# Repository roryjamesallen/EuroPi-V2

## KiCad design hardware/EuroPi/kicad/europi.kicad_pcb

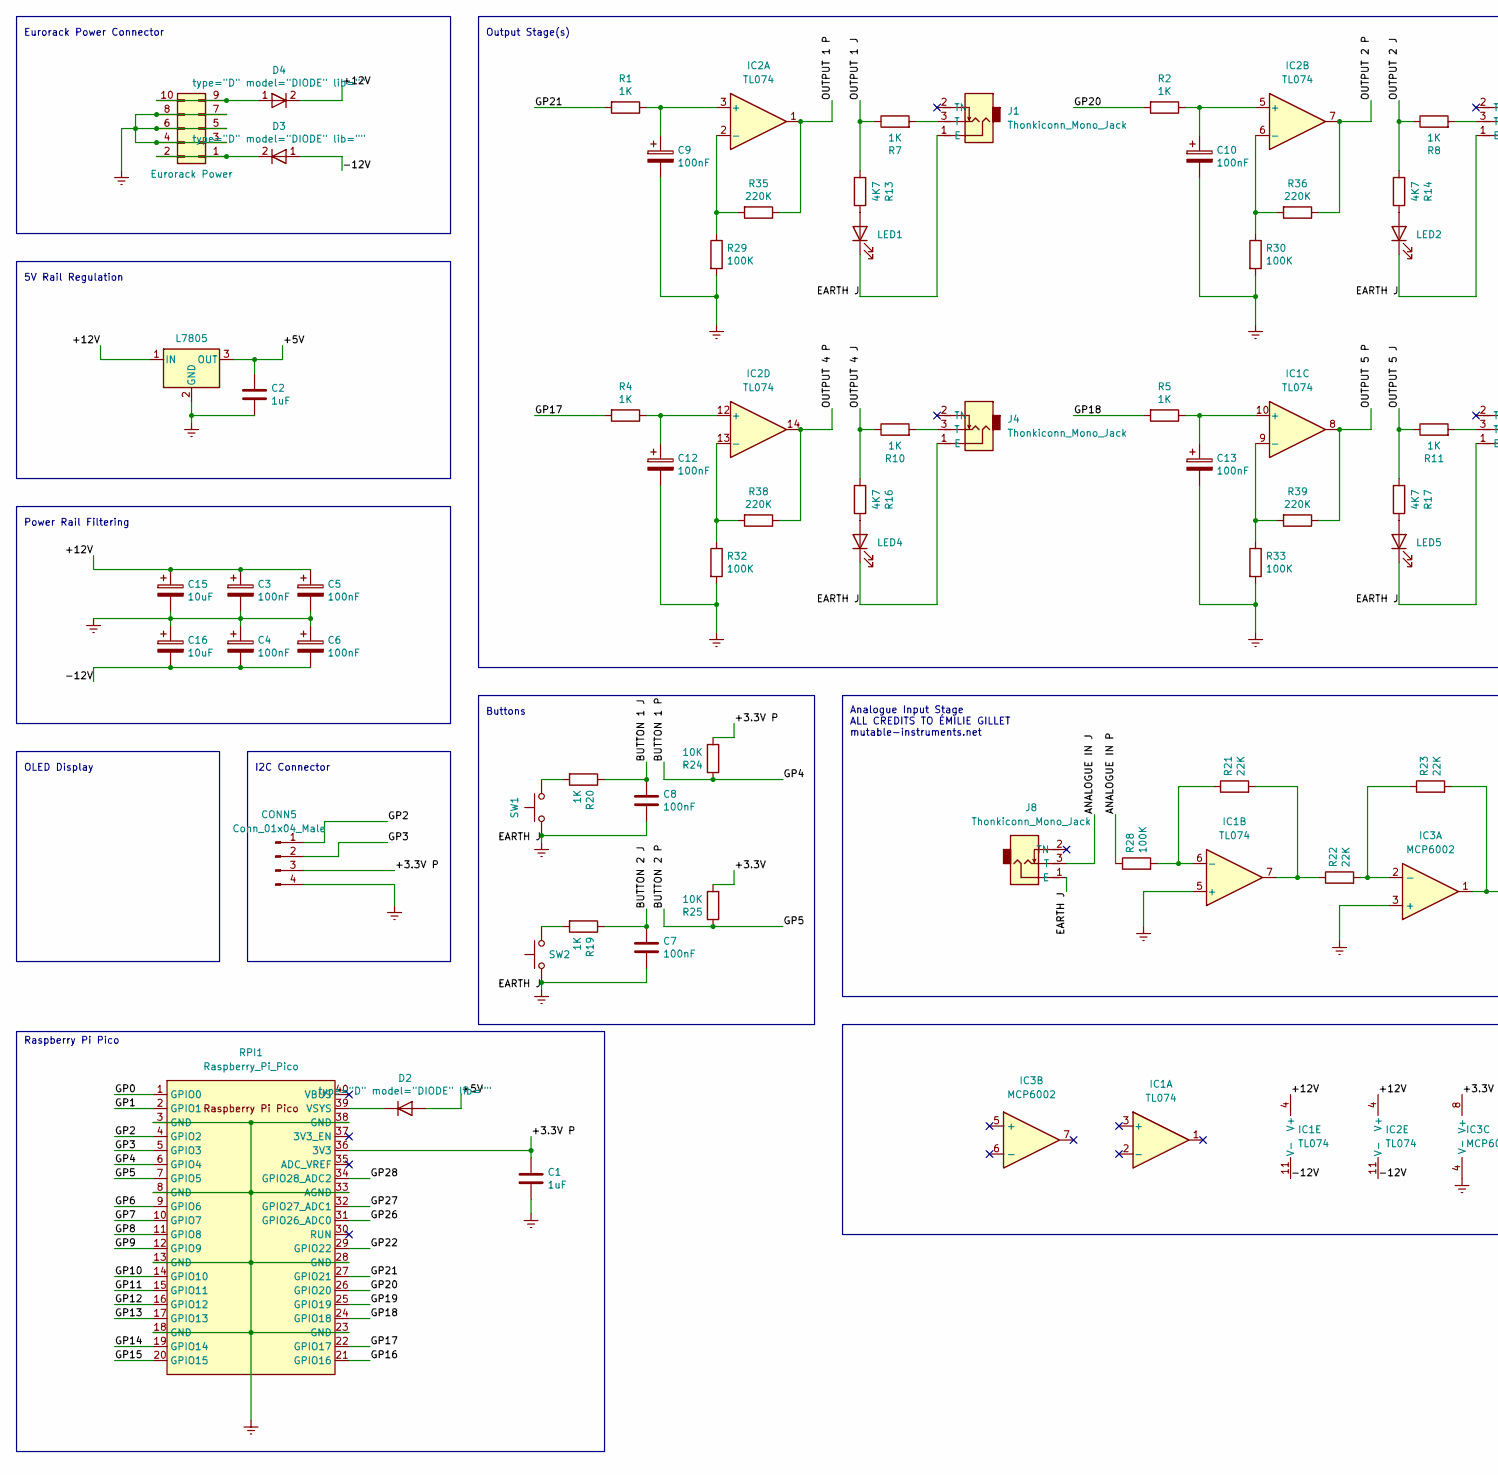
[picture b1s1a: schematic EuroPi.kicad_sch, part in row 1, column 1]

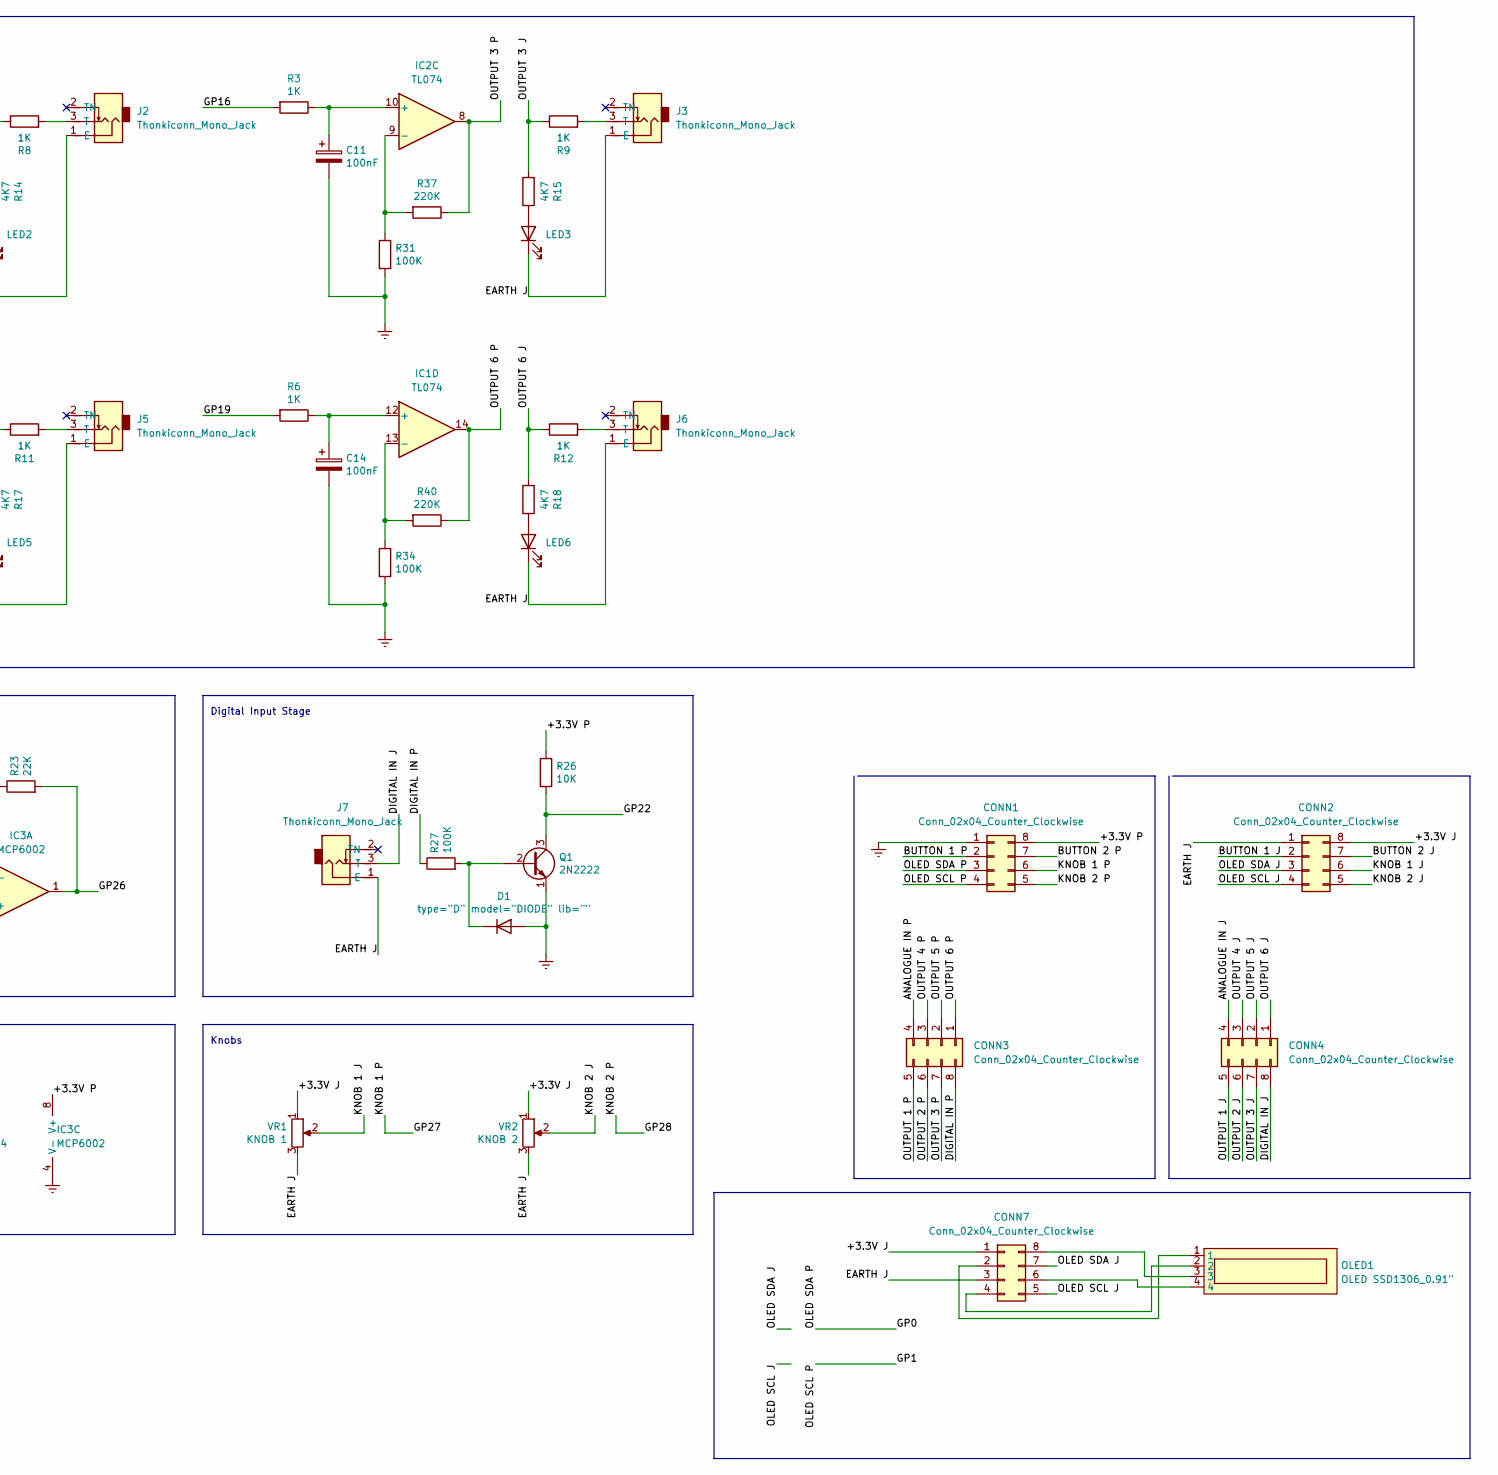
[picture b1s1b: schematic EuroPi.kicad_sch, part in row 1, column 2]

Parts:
C1, C2: 1uF; CP_Radial_D5.0mm_P2.50mm
C3, C4, C5, C6, C7, C8, C9, C10, C11, C12, C13, C14: 100nF; Capacitor Small Non-Polarised
C15, C16: 10uF; CP_Radial_D8.0mm_P3.80mm
CONN1, CONN2, CONN3, CONN4, CONN7: Conn_02x04_Counter_Clockwise; PinHeader_2x04_P2.54mm_Vertical
CONN5: Conn_01x04_Male; PinHeader_1x04_P2.54mm_Vertical
D1, D2, D3, D4: type="D" model="DIODE" lib=""; Schottky Diode
EuroPower1: Eurorack Power; Eurorack Power Header Unlabeled
IC1, IC2: TL074; DIP-14 IC Socket
IC3: MCP6002; DIP-8 IC Socket
J1, J2, J3, J4, J5, J6, J7, J8: Thonkiconn_Mono_Jack; Thonkiconn Mono Jack
LED1, LED2, LED3, LED4, LED5, LED6: LED; LED 3mm
OLED1: OLED SSD1306_0.91"; OLED SSD1306 0.91
Q1: 2N2222; TO-92
R1, R2, R3, R4, R5, R6, R7, R8, R9, R10, R11, R12, R19, R20: 1K; Resistor 0.25W Through-Hole
R13, R14, R15, R16, R17, R18: 4K7; Resistor 0.25W Through-Hole
R21, R22, R23: 22K; Resistor 0.25W Through-Hole
R24, R25, R26: 10K; Resistor 0.25W Through-Hole
R27, R28, R29, R30, R31, R32, R33, R34: 100K; Resistor 0.25W Through-Hole
R35, R36, R37, R38, R39, R40: 220K; Resistor 0.25W Through-Hole
REG1: L7805; TO-220-3_Vertical
RPI1: Raspberry_Pi_Pico; Raspberry Pi Pico
SW1, SW2: SW_Push; Switch Tactile Momentary C&K
VR1: KNOB 1; Potentiometer 9mm Vertical Linear Centred
VR2: KNOB 2; Potentiometer 9mm Vertical Linear Centred

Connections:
/+3.3V: R25.2
/+3.3V J: CONN2.8, CONN7.1, VR1.1, VR2.1
/+3.3V P: C1.1, CONN1.8, CONN5.3, IC3.8 (V+), R24.2, R26.1, RPI1.36 (3V3)
/+5V: C2.1, D2.1 (A), REG1.3 (OUT)
/+12V: C3.1, C5.1, C15.1, D4.2 (K), IC1.4 (V+), IC2.4 (V+), REG1.1 (IN)
/-12V: C4.2, C6.2, C16.2, D3.1 (A), IC1.11 (V-), IC2.11 (V-)
/ANALOGUE IN J: CONN4.4, J8.3 (T)
/ANALOGUE IN P: CONN3.4, R28.1
/BUTTON 1 J: C8.1, CONN2.2, R20.1
/BUTTON 1 P: CONN1.2, R24.1, RPI1.6 (GPIO4)
/BUTTON 2 J: C7.1, CONN2.7, R19.1
/BUTTON 2 P: CONN1.7, R25.1, RPI1.7 (GPIO5)
/DIGITAL IN J: CONN4.8, J7.3 (T)
/DIGITAL IN P: CONN3.8, R27.1
/GP0: CONN1.3, RPI1.1 (GPIO0)
/GP1: CONN1.4, RPI1.2 (GPIO1)
/GP2: CONN5.1, RPI1.4 (GPIO2)
/GP3: CONN5.2, RPI1.5 (GPIO3)
/GP6: RPI1.9 (GPIO6)
/GP7: RPI1.10 (GPIO7)
/GP8: RPI1.11 (GPIO8)
/GP9: RPI1.12 (GPIO9)
/GP10: RPI1.14 (GPIO10)
/GP11: RPI1.15 (GPIO11)
/GP12: RPI1.16 (GPIO12)
/GP13: RPI1.17 (GPIO13)
/GP14: RPI1.19 (GPIO14)
/GP15: RPI1.20 (GPIO15)
/GP16: R3.2, RPI1.21 (GPIO16)
/GP17: R4.2, RPI1.22 (GPIO17)
/GP18: R5.2, RPI1.24 (GPIO18)
/GP19: R6.2, RPI1.25 (GPIO19)
/GP20: R2.2, RPI1.26 (GPIO20)
/GP21: R1.2, RPI1.27 (GPIO21)
/GP22: Q1.3 (C), R26.2, RPI1.29 (GPIO22)
/GP26: IC3.1, R23.2, RPI1.31 (GPIO26_ADC0)
/GP27: CONN1.6, RPI1.32 (GPIO27_ADC1)
/GP28: CONN1.5, RPI1.34 (GPIO28_ADC2)
/KNOB 1 J: CONN2.6, VR1.2
/KNOB 2 J: CONN2.5, VR2.2
/OLED SCL J: CONN2.4, CONN7.5
/OLED SDA J: CONN2.3, CONN7.7
/OUTPUT 1 J: CONN4.5, R7.1, R13.2
/OUTPUT 1 P: CONN3.5, IC2.1, R35.1
/OUTPUT 2 J: CONN4.6, R8.1, R14.2
/OUTPUT 2 P: CONN3.6, IC2.7, R36.1
/OUTPUT 3 J: CONN4.7, R9.1, R15.2
/OUTPUT 3 P: CONN3.7, IC2.8, R37.1
/OUTPUT 4 J: CONN4.3, R10.1, R16.2
/OUTPUT 4 P: CONN3.3, IC2.14, R38.1
/OUTPUT 5 J: CONN4.2, R11.1, R17.2
/OUTPUT 5 P: CONN3.2, IC1.8, R39.1
/OUTPUT 6 J: CONN4.1, R12.1, R18.2
/OUTPUT 6 P: CONN3.1, IC1.14, R40.1
unnamed: CONN7.2, OLED1.1
unnamed: CONN7.4, OLED1.2
unnamed: CONN7.6, OLED1.4
unnamed: CONN7.8, OLED1.3
unnamed: D1.2 (K), Q1.2 (B), R27.2
unnamed: D2.2 (K), RPI1.39 (VSYS)
unnamed: D3.2 (K), EuroPower1.1, EuroPower1.2
unnamed: D4.1 (A), EuroPower1.9, EuroPower1.10
unnamed: IC1.7, R21.2, R22.1
unnamed: IC1.6 (-), R21.1, R28.2
unnamed: C13.1, IC1.10 (+), R5.1
unnamed: IC1.9 (-), R33.1, R39.2
unnamed: C14.1, IC1.12 (+), R6.1
unnamed: IC1.13 (-), R34.1, R40.2
unnamed: C9.1, IC2.3 (+), R1.1
unnamed: IC2.2 (-), R29.1, R35.2
unnamed: C10.1, IC2.5 (+), R2.1
unnamed: IC2.6 (-), R30.1, R36.2
unnamed: C11.1, IC2.10 (+), R3.1
unnamed: IC2.9 (-), R31.1, R37.2
unnamed: C12.1, IC2.12 (+), R4.1
unnamed: IC2.13 (-), R32.1, R38.2
unnamed: IC3.2 (-), R22.2, R23.1
unnamed: J1.3 (T), R7.2
unnamed: J2.3 (T), R8.2
unnamed: J3.3 (T), R9.2
unnamed: J4.3 (T), R10.2
unnamed: J5.3 (T), R11.2
unnamed: J6.3 (T), R12.2
unnamed: LED1.2 (A), R13.1
unnamed: LED2.2 (A), R14.1
unnamed: LED3.2 (A), R15.1
unnamed: LED4.2 (A), R16.1
unnamed: LED5.2 (A), R17.1
unnamed: LED6.2 (A), R18.1
unnamed: R19.2, SW2.2
unnamed: R20.2, SW1.2

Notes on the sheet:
OLED Display
Buttons
5V Rail Regulation
Analogue Input Stage ALL CREDITS TO ÉMILIE GILLET mutable-instruments.net
Power Rail Filtering
Eurorack Power Connector
I2C Connector
Digital Input Stage
Raspberry Pi Pico
Output Stage(s)
Knobs

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
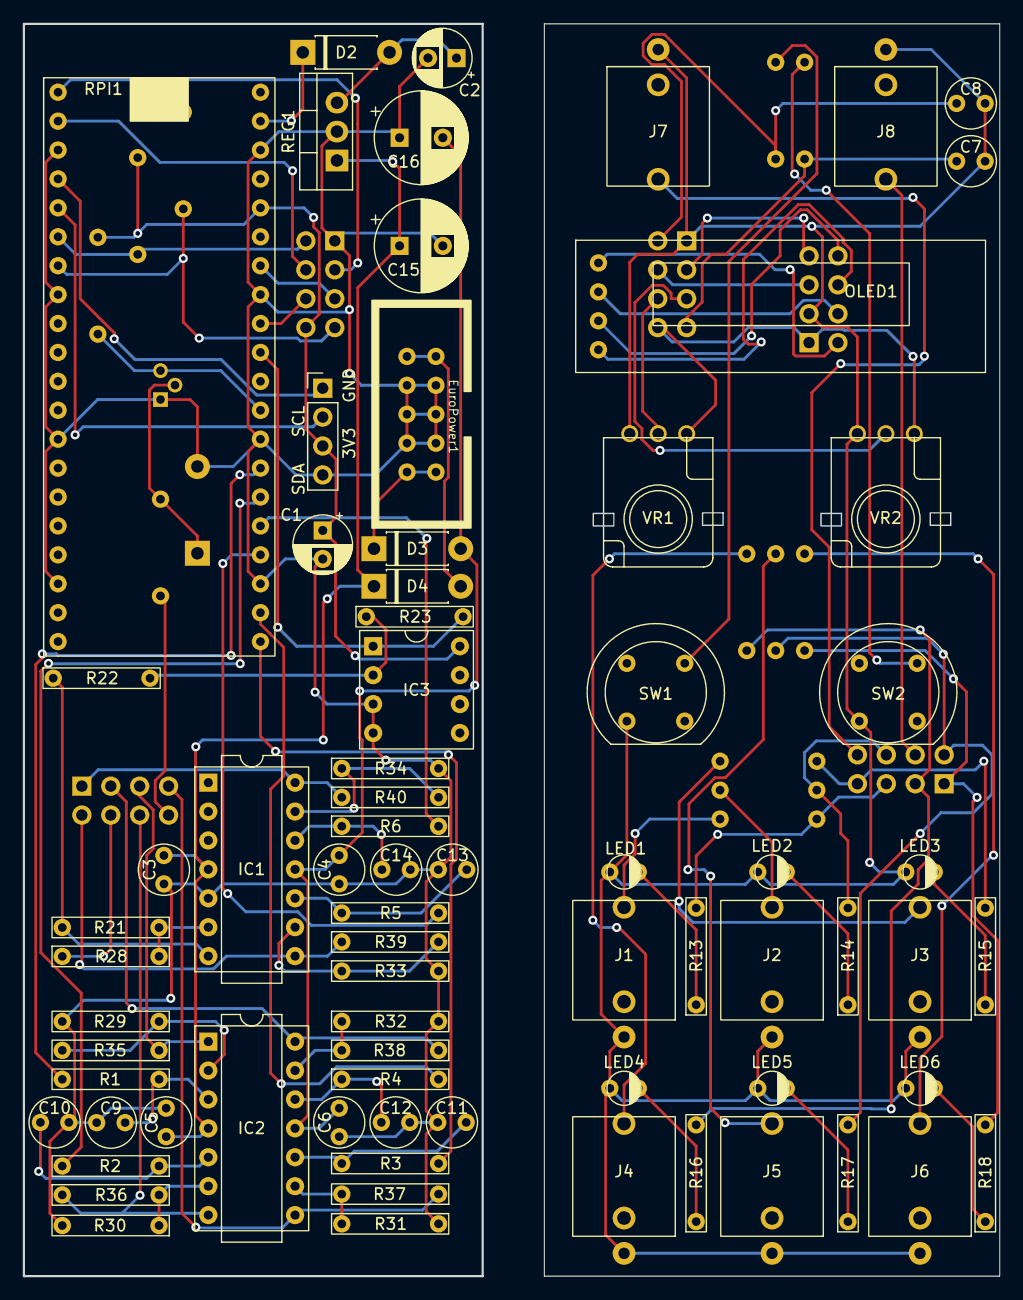
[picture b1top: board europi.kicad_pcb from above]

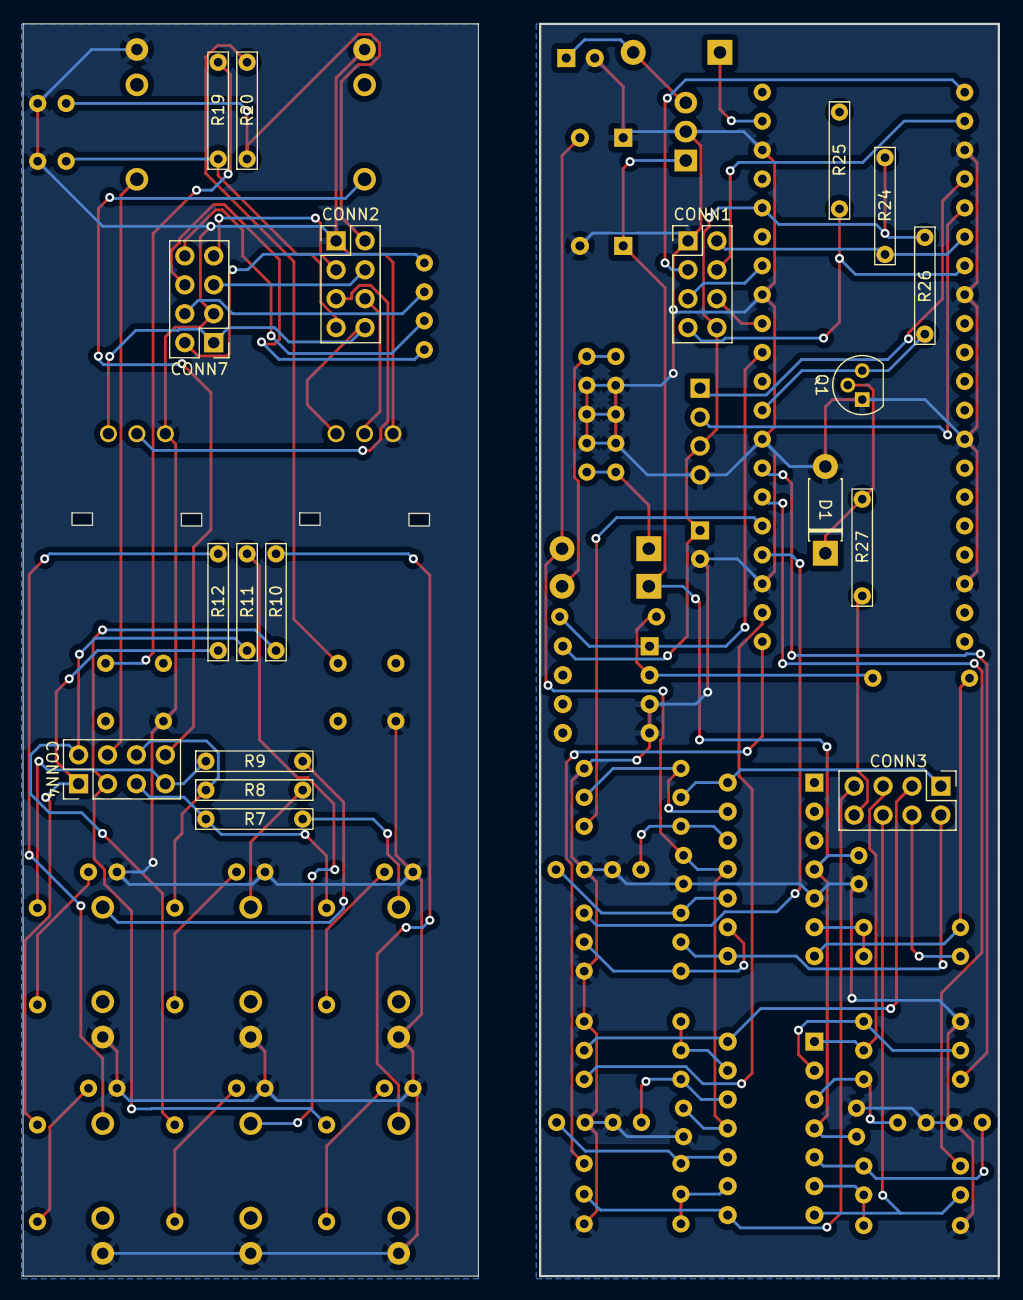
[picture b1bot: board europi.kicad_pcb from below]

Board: 2 copper layers, 85.6 x 110.0 mm, 92 parts (19 on the bottom side), 82 nets.

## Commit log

2025-01-26 Fix a bug where the settings menu wasn't properly locking & unlocking the items of a KnobBank
2025-01-26 Set the initial lock value of the 'choice' level knob to be the current value
2025-01-26 Move the dynamic knob-locking into the menu items themselves
2025-01-26 Add a function to change the lock value of a locked knob. Revert to keeping the knob lock logic contained to one place
2025-01-26 Formatting
2025-01-26 Use lockable knobs for the configuration editors
2025-01-27 Initial implementation of binary counter sequencer
2025-01-31 Initial commit. Basic skeleton works. Need to implement UI to let user enter the letters
2025-01-31 Add patch ideas
2025-01-31 Implement the UI so we can pick letters. Fix saving the state
2025-01-31 Add Morse to menu, readme
2025-01-31 Make newlines consistent throughout the readme
2025-01-31 Add missing scripts to readme, fix alphabetical ordering
2025-01-31 Promote Coin Toss & Scope to regular scripts, remove proof-of-concept scripts from the main menu, but leave them in a commented-out section
2025-01-31 Use K2 to select the letter, B1 and B2 to change it. This avoids issues with the knob accidentally unlocking while scrolling across letters. It also simplifies things by eliminating the KnobBank comp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

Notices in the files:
hardware/EuroPi/kicad/EuroPi.kicad_sch:
CC BY-SA 3.0
